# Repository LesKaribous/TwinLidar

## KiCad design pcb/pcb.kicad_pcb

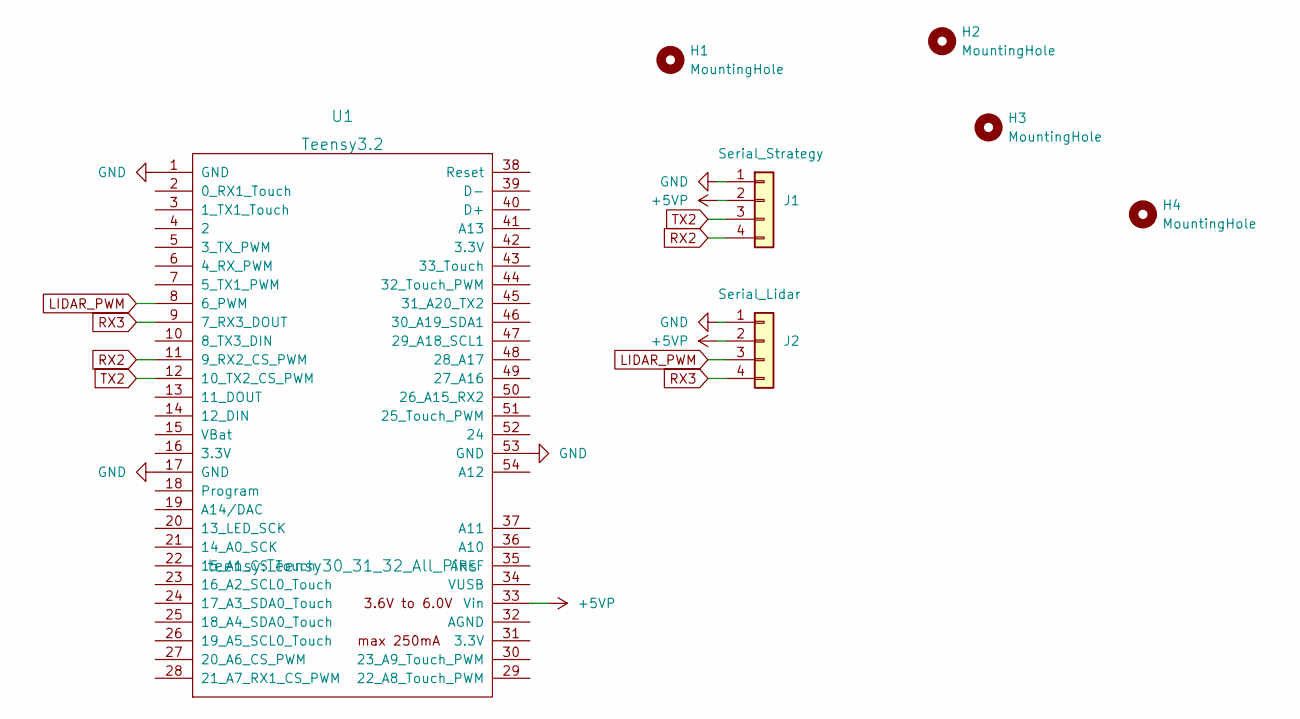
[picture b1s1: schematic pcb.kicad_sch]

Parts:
H1, H2, H3, H4: MountingHole; MountingHole_3.2mm_M3
J1: Serial_Strategy; Molex_KK-254_AE-6410-04A_1x04_P2.54mm_Vertical
J2: Serial_Lidar; Molex_KK-254_AE-6410-04A_1x04_P2.54mm_Vertical
U1: Teensy3.2; Teensy30_31_32_All_Pins

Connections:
+5VP: J1.2, J2.2, U1.33 (Vin)
GND: J1.1, J2.1, U1.1 (GND), U1.17 (GND), U1.53 (GND)
LIDAR_PWM: J2.3, U1.8 (6_PWM)
RX2: J1.4, U1.11 (9_RX2_CS_PWM)
RX3: J2.4, U1.9 (7_RX3_DOUT)
TX2: J1.3, U1.12 (10_TX2_CS_PWM)

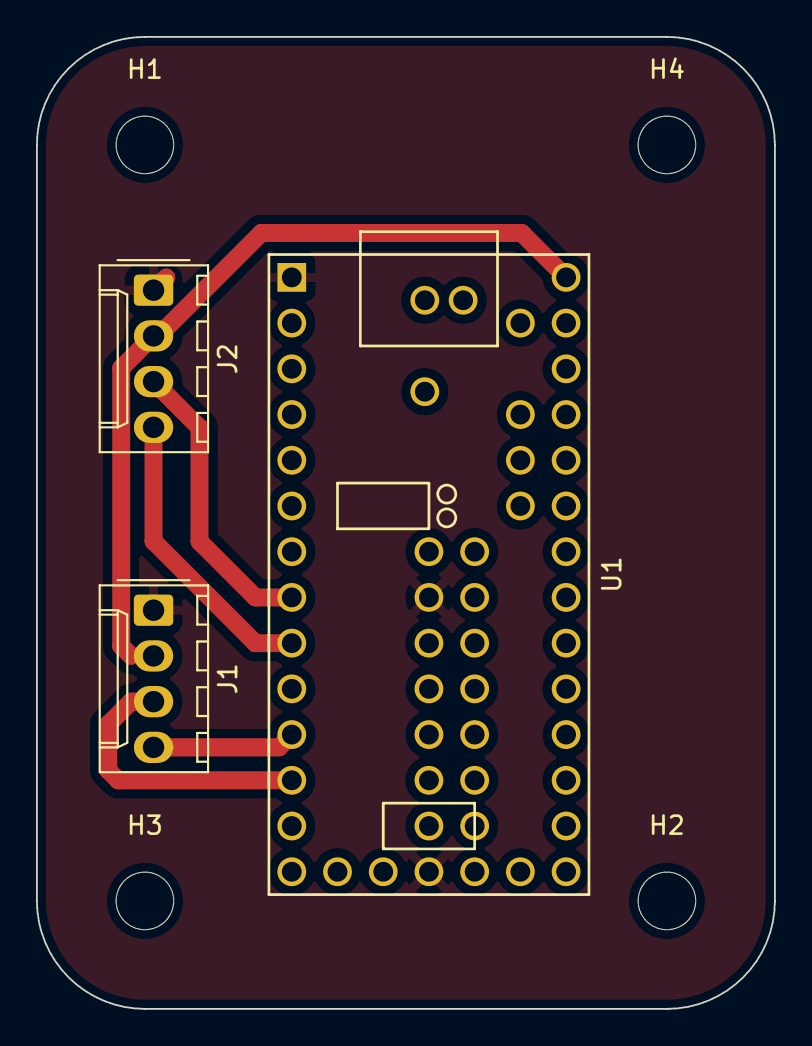
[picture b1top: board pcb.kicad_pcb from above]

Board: 2 copper layers, 41.0 x 54.0 mm, 7 parts (0 on the bottom side), 6 nets.

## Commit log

2022-05-02 init : Add main architecture
2022-05-02 Add PCB
2022-05-02 Update : Lidar parsing
2022-05-12 feat(LD06) : Add data parser
2022-05-12 feat(Sim) : Add processing lidar simulation
2022-05-14 saving night works
2022-05-16 save current state
2022-05-16 update Detection
2022-05-18 fix Intercom
2022-05-18 fix Lidar
2022-05-21 fix(Intercom & Debugger)
2022-05-22 feat(Lidar) : Lidar parsing filtering
2022-05-22 feat(Debugger) : Add debug level
2022-05-22 remove(Geometry) : Remove useless part
2022-05-22 fix(Debugger) : Apply previous changes to the whole code
2022-05-23 minor changes
2022-05-23 fix Collision
2022-05-25 feat(global) : Team changing
2022-09-25 thomas's update of processing code
2022-09-25 add sim Lidar
2022-09-25 update folder name to LidarSim
2022-09-25 Add map to Lidar Sim
2022-09-25 Add table
2023-03-01 solve reflectors location issue
2023-03-29 upload LidarSim V2
2023-03-30 Fix PlatformIO project not opening in VS Code
2023-04-03 Centralize rays for each lidar
2023-04-03 add robot location XML parsing
2023-04-03 add instanciation
2023-04-03 add XML and reflectors modifications
2023-04-03 update translation, need to be modified
2023-04-10 refactor(Global) : Refactor TwinLidar based on the LD06 library
2023-04-10 refactor(LidarView) : Refactor Lidar and LidarView to match the Teleplot syntax
2023-04-10 feat(Lidar) : Implement sectoring
2023-04-14 feat(LED) : Implement real-time LED feedback
2023-04-16 feat(Lidar) : Implement Communication, LidarView, LedRing
2023-04-18 feat(Intercom) : Add async Request
2023-04-19 fix(Lidar) : fix avoidance request handling
2023-04-19 fix(Lidar) : Intercom & Command
2023-04-21 display heading
2023-04-21 increase detection radius
2023-04-21 release Belgium 2023
2023-05-17 pre-release2023
2023-05-18 feat(Lidar) : Add adaptative fov
2024-02-18 Change Math to math for linux compatibility (case sensitive)
2024-03-27 wip(Performance)
2024-04-07 wip(Global)
2024-04-07 feat(intercom) : rework intercom with crc
2024-04-07 fix(InterCom) : Fiability
2024-04-07 test(InterCom) : StressTest
2024-04-07 clean(Test) : Clean Test
2024-04-07 fix(Fix)
2024-04-08 fix(Test)
2024-04-09 test(Intercom) : This is a stupid way to update ihm
2024-04-11 lidar
2024-04-11 getDistance
2024-04-11 safety
2024-04-13 night
2024-04-15 fiability
2024-04-19 fix detection
2024-04-20 margin
2024-05-01 lidar fiability
2024-05-06 adaptative detectino
2025-05-16 mcu(core) : Add support for Teensy 4.0
2025-05-17 screen
2025-05-17 feat(occupancyMap)
2025-05-17 feat(occumpacy) : Add static occupancy maps
2025-05-20 fix(Intercom)
